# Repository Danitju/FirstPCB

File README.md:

# FirstPCB
 My first try at making a 2x2 macro pcb

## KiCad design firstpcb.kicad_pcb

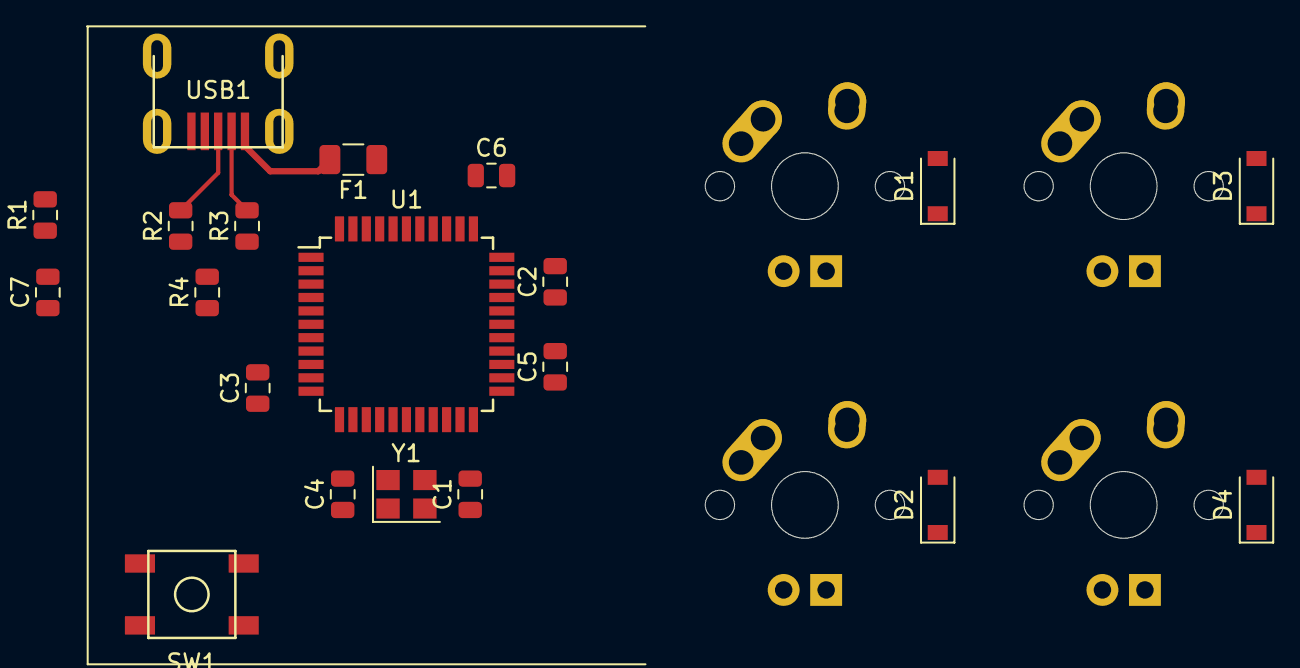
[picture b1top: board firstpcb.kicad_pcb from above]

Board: 2 copper layers, 24 parts (0 on the bottom side), 19 nets.

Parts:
C1, C2: 22pF; C_0805_2012Metric
C3: 1uF; C_0805_2012Metric
C4, C5, C6: 0.1uF; C_0805_2012Metric
C7: 10uF; C_0805_2012Metric
D1, D2, D3, D4: SOD-123; D_SOD-123
F1: 500mA; Fuse_1206_3216Metric
MX1, MX2, MX3, MX4: MX-NoLED; MX-1U
R1, R4: 10k; R_0805_2012Metric
R2, R3: 22; R_0805_2012Metric
SW1: SW_Push; SKQG-1155865
U1: ATmega32U4-AU; TQFP-44_10x10mm_P0.8mm
USB1: Molex-0548190589
Y1: 16MHz; Crystal_SMD_3225-4Pin_3.2x2.5mm

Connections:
+5V: C4.1, C5.1, C6.1, C7.1, F1.1, R1.1, U1.2, U1.7, U1.14, U1.24, U1.34, U1.44
COL0: MX1.1, MX3.1, U1.29
COL1: MX2.1, MX4.1, U1.28
D+: R2.2, USB1.3
D-: R3.2, USB1.4
GND: C1.2, C2.1, C2.2, C3.2, C4.2, C5.2, C6.2, C7.2, R4.1, SW1.1, U1.5, U1.15, U1.16, U1.23, U1.35, U1.43, USB1.1, Y1.2, Y1.3, Y1.4
unnamed: C1.1, U1.17, Y1.1
unnamed: C3.1, U1.6
unnamed: D1.2, MX1.2
unnamed: D2.2, MX3.2
unnamed: D3.2, MX2.2
unnamed: D4.2, MX4.2
unnamed: R1.2, SW1.2, U1.13
unnamed: R2.1, U1.4
unnamed: R3.1, U1.3
unnamed: R4.2, U1.33
ROW0: D1.1, D3.1, U1.27
ROW1: D2.1, D4.1, U1.30
VCC: F1.2, USB1.5

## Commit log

2022-10-04 First files
2022-10-04 Added the submodules
2022-10-04 Added footprint libs
2022-10-04 Created the MCU zone
2022-10-04 Renaming footprints
2022-10-04 First pcb export nothing changed yet
2022-10-04 d1-d4 placed on switches
2022-10-05 Little bit of routing done
